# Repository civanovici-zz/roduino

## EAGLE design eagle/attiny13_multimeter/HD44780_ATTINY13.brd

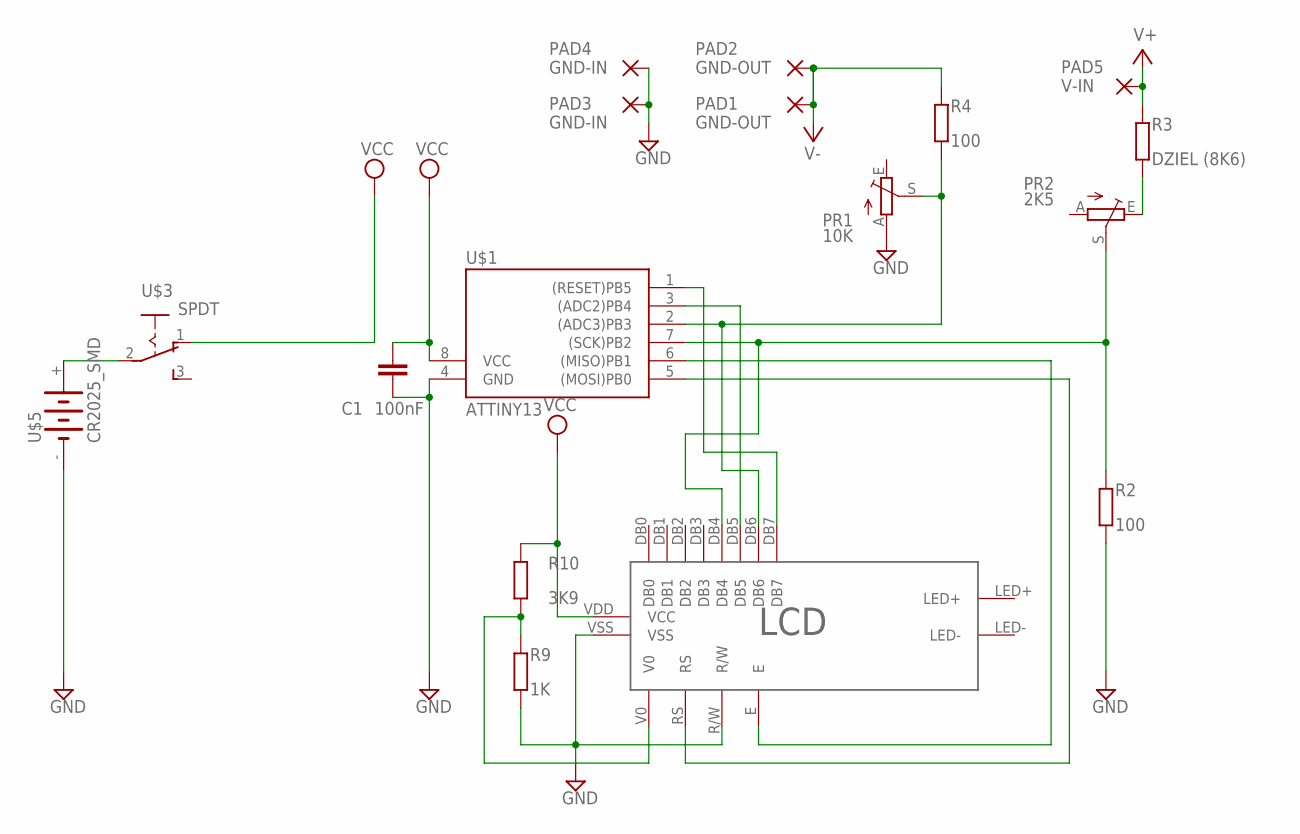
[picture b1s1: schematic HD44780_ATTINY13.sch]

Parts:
C1: 100nF; C0805
PAD1, PAD2: GND-OUT; 2,54/0,8
PAD3, PAD4: GND-IN; 2,54/0,8
PAD5: V-IN; 2,54/0,8
PR1: 10K; CA6V
PR2: 2K5; CA6V
R2, R4: 100; R0805
R3: DZIEL (8K6); R0805
R9: 1K; R0805
R10: 3K9; R0805
U$1: ATTINY13; SO08
U$2: LGDM1602N1; GDM1602N1
U$3: SPDT
U$5: CR2025_SMD

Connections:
GND: C1.2, PAD3.1, PAD4.1, PR1.A, R2.1, R9.1, U$1.4 (GND), U$2.R/W, U$2.VSS, U$5.-
unnamed: R9.2, R10.1, U$2.V0
unnamed: U$1.3 ((ADC2)PB4), U$2.DB5
unnamed: PR2.E, R3.1
unnamed: U$3.2, U$5.+
unnamed: U$1.1 ((RESET)PB5), U$2.DB7
unnamed: U$1.6 ((MISO)PB1), U$2.E
unnamed: U$1.5 ((MOSI)PB0), U$2.RS
unnamed: PR1.S, R4.1, U$1.2 ((ADC3)PB3), U$2.DB6
unnamed: PR2.S, R2.2, U$1.7 ((SCK)PB2), U$2.DB4
V+: PAD5.1, R3.2
V-: PAD1.1, PAD2.1, R4.2
VBUS: U$3.1 (O)
VCC: C1.1, R10.2, U$1.8 (VCC), U$2.VDD (VCC)

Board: 2 copper layers, 17 parts (5 on the bottom side), 13 nets, no tracks yet.

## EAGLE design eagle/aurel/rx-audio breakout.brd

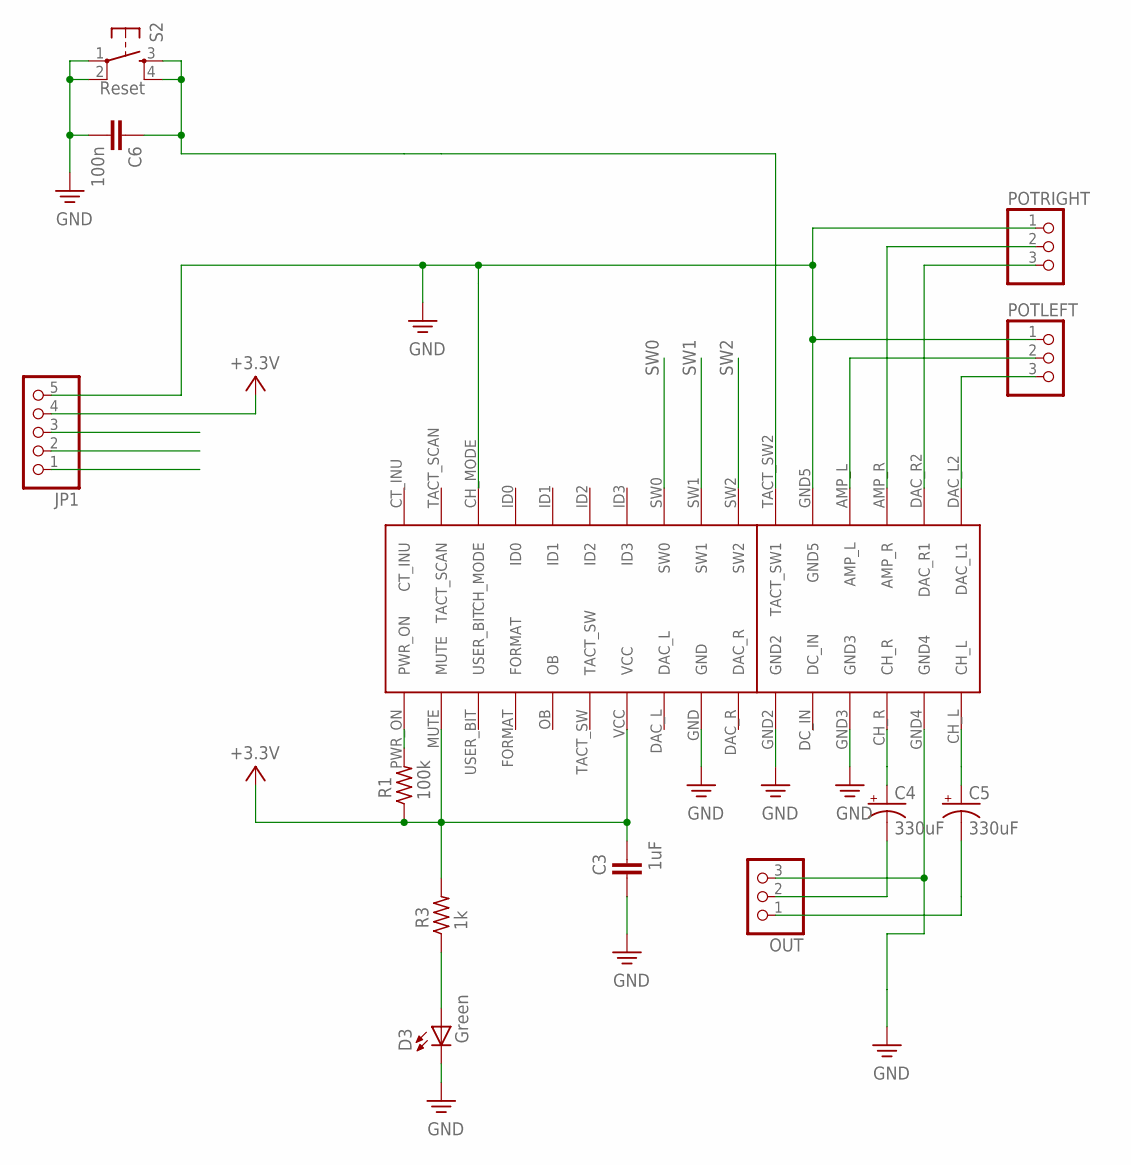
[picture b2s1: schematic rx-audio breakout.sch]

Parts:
C3: 1uF; 0805A
C4, C5: 330uF; SMC_D
C6: 100n; C0805
D3: Green; LED-0603
JP1: PINHD-1X5; 1X05
OUT: PINHD-1X3; 1X03
POTLEFT: PINHD-1X3; 1X03
POTRIGHT: PINHD-1X3; 1X03
R1: 100k; 0805A
R3: 1k; 0805A
S2: Reset; TACTILE_SWITCH_SMD
U$1: RX-AUDIO-2.4VERTICAL; AUREL_RX-AUDIO-2.4GH-TRH

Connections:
GND: C3.+ (1), C6.2, D3.C, JP1.5, OUT.3, POTLEFT.1, POTRIGHT.1, S2.1, S2.2, U$1.CH_MODE, U$1.GND, U$1.GND2, U$1.GND3, U$1.GND4, U$1.GND5
LINE_IN: C5.-, OUT.1
N2: C6.1, S2.3, S2.4, U$1.TACT_SW2 (TACT_SW1)
unnamed: C4.+, U$1.CH_R
unnamed: C5.+, U$1.CH_L
unnamed: POTLEFT.2, U$1.AMP_L
unnamed: D3.A, R3.+ (1)
unnamed: R1.- (2), U$1.PWR_ON
unnamed: POTLEFT.3, U$1.DAC_L2 (DAC_L1)
unnamed: POTRIGHT.3, U$1.DAC_R2 (DAC_R1)
unnamed: POTRIGHT.2, U$1.AMP_R
unnamed: C4.-, OUT.2
SW0: JP1.1, U$1.SW0
SW1: JP1.2, U$1.SW1
SW2: JP1.3, U$1.SW2
VCC: C3.- (2), JP1.4, R1.+ (1), R3.- (2), U$1.MUTE, U$1.VCC

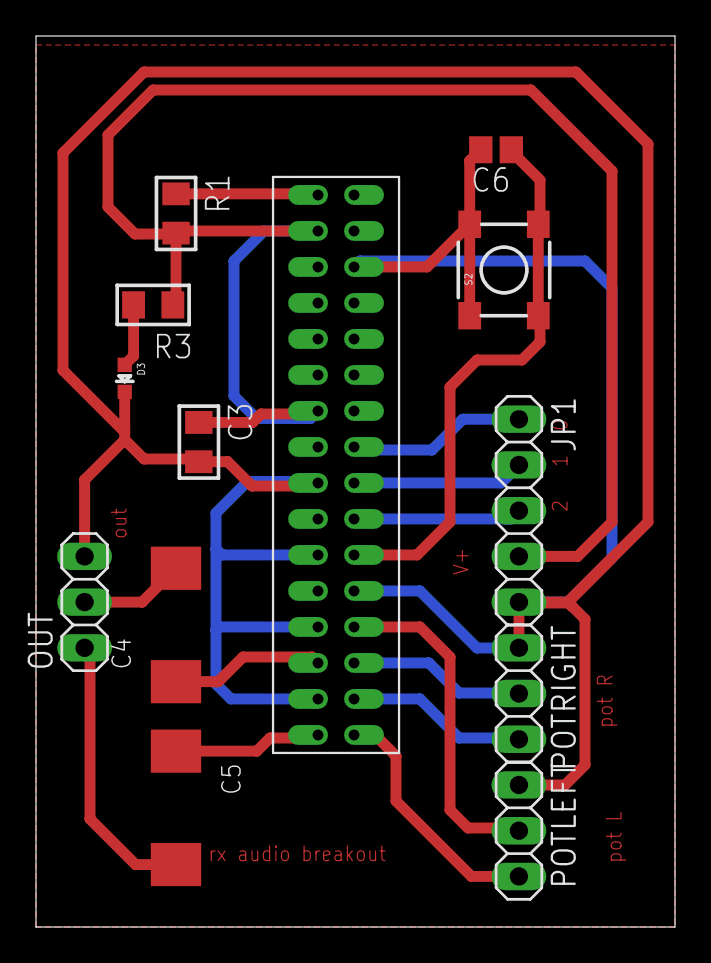
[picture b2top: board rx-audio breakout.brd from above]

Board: 2 copper layers, 35.5 x 49.5 mm, 13 parts (0 on the bottom side), 16 nets.

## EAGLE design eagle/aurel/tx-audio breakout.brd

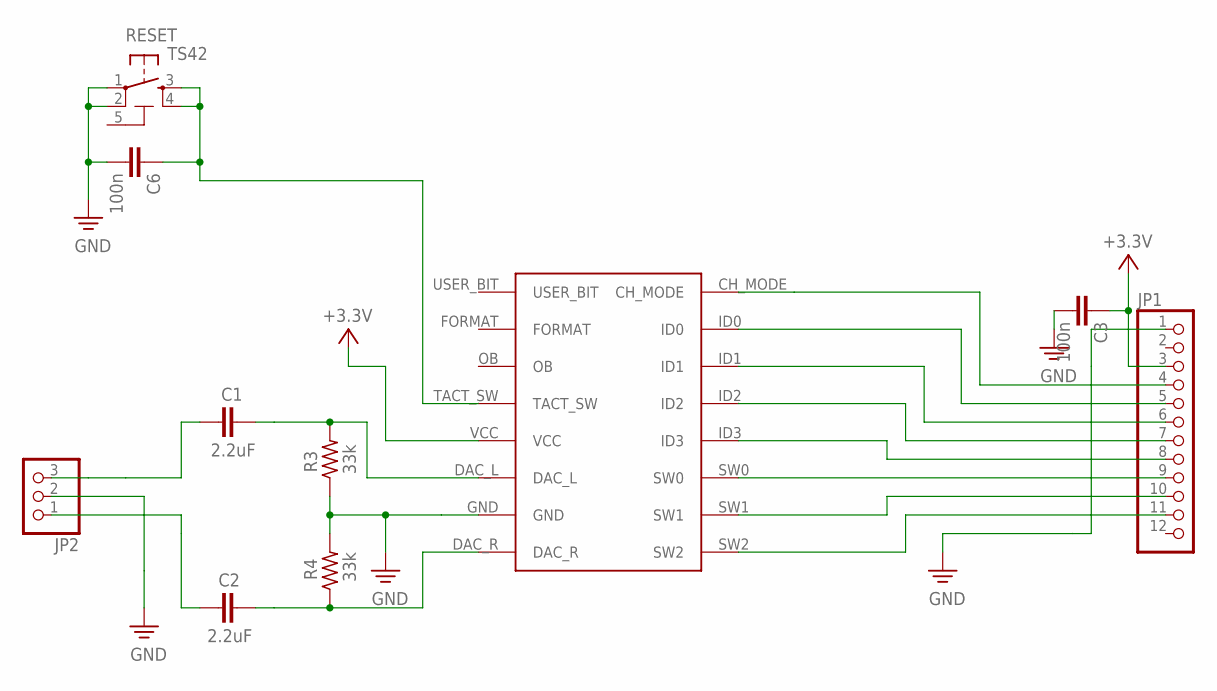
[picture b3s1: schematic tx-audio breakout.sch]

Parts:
C1, C2: 2.2uF; 0805A
C3, C6: 100n; C0805
JP1: PINHD-1X12; 1X12
JP2: PINHD-1X3; 1X03
R3, R4: 33k; 0805A
RESET: TS42
U$1: TX-AUDIO-2.4VERTICAL; AUREL-TX-AUDIO-2.4GH-TRH

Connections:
5-GND: RESET.5 (5-GND)
GND: C3.2, C6.2, JP1.1, JP2.2, R3.+ (1), R4.- (2), RESET.1, RESET.2, U$1.GND
LINE_IN: C1.+ (1), JP2.3
N2: C6.1, RESET.3, RESET.4, U$1.TACT_SW
unnamed: JP1.10, U$1.SW1
unnamed: JP1.11, U$1.SW2
unnamed: JP1.9, U$1.SW0
unnamed: C1.- (2), R3.- (2), U$1.DAC_L
unnamed: JP1.8, U$1.ID3
unnamed: JP1.7, U$1.ID2
unnamed: JP1.6, U$1.ID1
unnamed: JP1.5, U$1.ID0
unnamed: JP1.4, U$1.CH_MODE
unnamed: C2.- (2), JP2.1
unnamed: C2.+ (1), R4.+ (1), U$1.DAC_R
VCC: C3.1, JP1.3, U$1.VCC

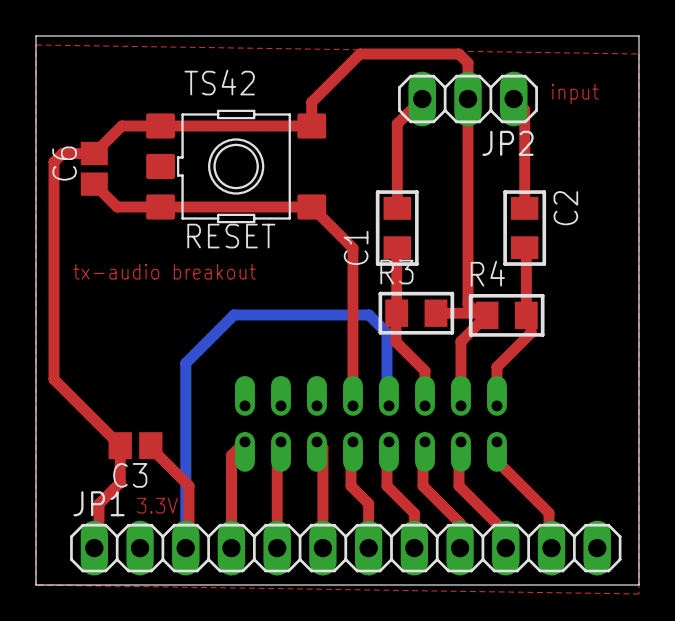
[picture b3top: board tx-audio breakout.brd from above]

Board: 2 copper layers, 33.5 x 30.5 mm, 10 parts (1 on the bottom side), 15 nets.

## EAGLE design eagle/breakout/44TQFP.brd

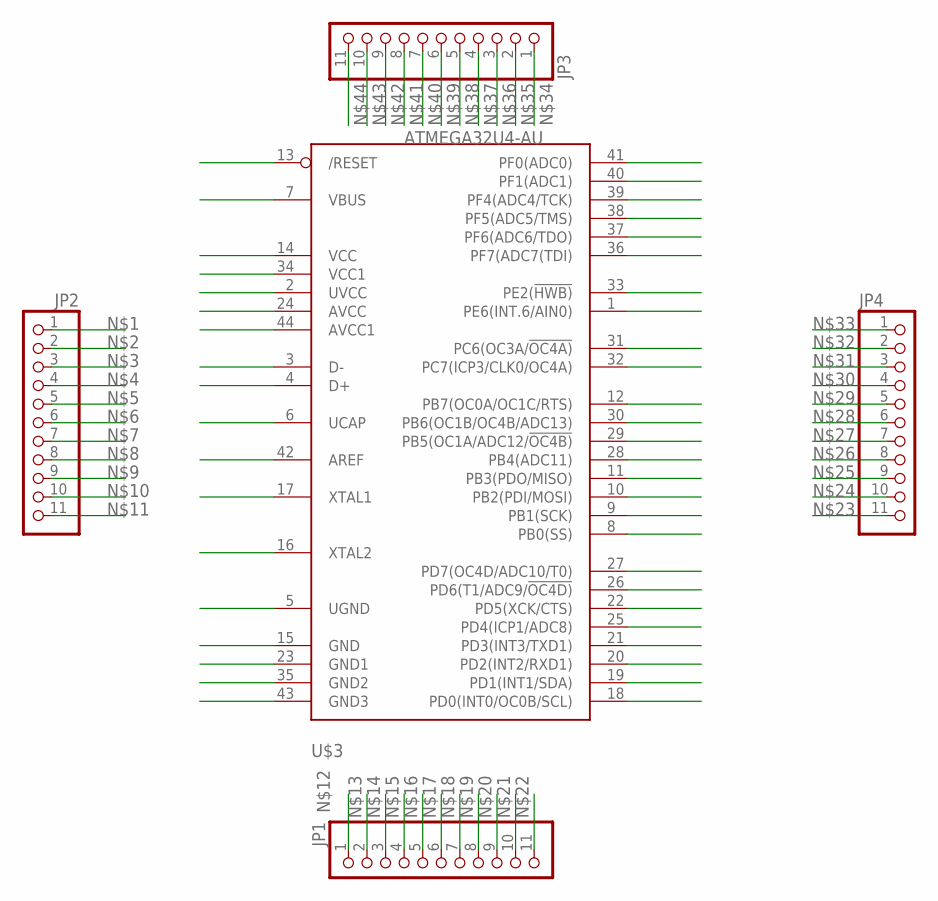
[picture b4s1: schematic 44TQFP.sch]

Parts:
JP1, JP2, JP3, JP4: PINHD-1X11; 1X11
U$3: ATMEGA32U4-AU; TQFP44

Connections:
unnamed: JP2.1, U$3.1 (PE6(INT.6/AIN0))
unnamed: JP2.2, U$3.2 (UVCC)
unnamed: JP2.3, U$3.3 (D-)
unnamed: JP2.4, U$3.4 (D+)
unnamed: JP2.5, U$3.5 (UGND)
unnamed: JP2.6, U$3.6 (UCAP)
unnamed: JP2.7, U$3.7 (VBUS)
unnamed: JP2.8, U$3.8 (PB0(SS))
unnamed: JP2.9, U$3.9 (PB1(SCK))
unnamed: JP2.10, U$3.10 (PB2(PDI/MOSI))
unnamed: JP2.11, U$3.11 (PB3(PDO/MISO))
unnamed: JP1.1, U$3.12 (PB7(OC0A/OC1C/RTS))
unnamed: JP1.2, U$3.13 (/RESET)
unnamed: JP1.3, U$3.14 (VCC)
unnamed: JP1.4, U$3.15 (GND)
unnamed: JP1.5, U$3.16 (XTAL2)
unnamed: JP1.6, U$3.17 (XTAL1)
unnamed: JP1.7, U$3.18 (PD0(INT0/OC0B/SCL))
unnamed: JP1.8, U$3.19 (PD1(INT1/SDA))
unnamed: JP1.9, U$3.20 (PD2(INT2/RXD1))
unnamed: JP1.10, U$3.21 (PD3(INT3/TXD1))
unnamed: JP1.11, U$3.22 (PD5(XCK/CTS))
unnamed: JP4.11, U$3.23 (GND1)
unnamed: JP4.10, U$3.24 (AVCC)
unnamed: JP4.9, U$3.25 (PD4(ICP1/ADC8))
unnamed: JP4.8, U$3.26 (PD6(T1/ADC9/!OC4D))
unnamed: JP4.7, U$3.27 (PD7(OC4D/ADC10/T0))
unnamed: JP4.6, U$3.28 (PB4(ADC11))
unnamed: JP4.5, U$3.29 (PB5(OC1A/ADC12/!OC4B))
unnamed: JP4.4, U$3.30 (PB6(OC1B/OC4B/ADC13))
unnamed: JP4.3, U$3.31 (PC6(OC3A/!OC4A))
unnamed: JP4.2, U$3.32 (PC7(ICP3/CLK0/OC4A))
unnamed: JP4.1, U$3.33 (PE2(!HWB))
unnamed: JP3.1, U$3.34 (VCC1)
unnamed: JP3.2, U$3.35 (GND2)
unnamed: JP3.3, U$3.36 (PF7(ADC7(TDI))
unnamed: JP3.4, U$3.37 (PF6(ADC6/TDO))
unnamed: JP3.5, U$3.38 (PF5(ADC5/TMS))
unnamed: JP3.6, U$3.39 (PF4(ADC4/TCK))
unnamed: JP3.7, U$3.40 (PF1(ADC1))
unnamed: JP3.8, U$3.41 (PF0(ADC0))
unnamed: JP3.9, U$3.42 (AREF)
unnamed: JP3.10, U$3.43 (GND3)
unnamed: JP3.11, U$3.44 (AVCC1)

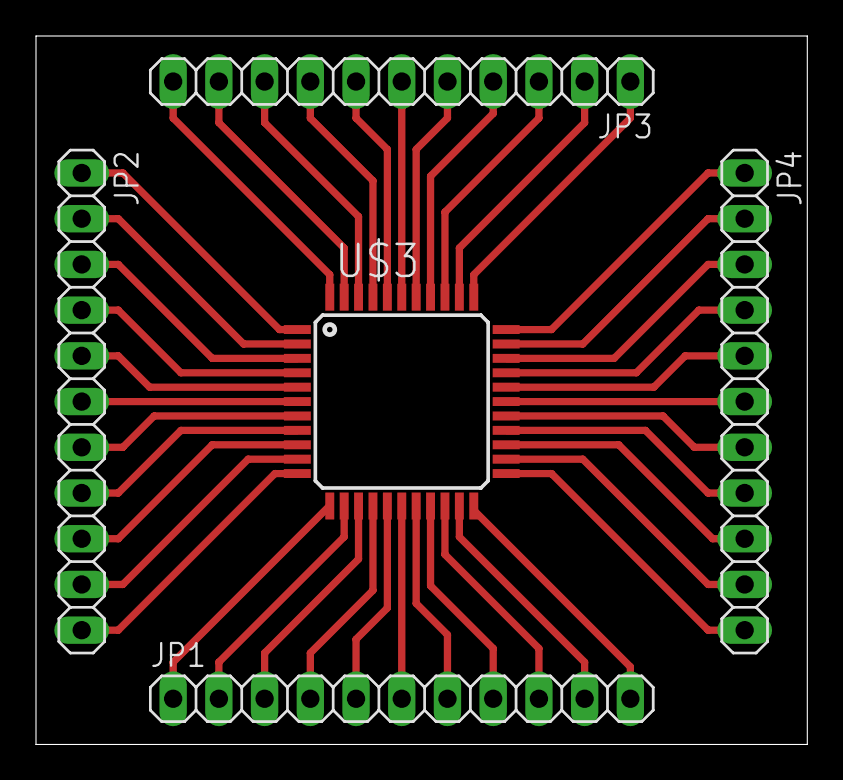
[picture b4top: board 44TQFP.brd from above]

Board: 2 copper layers, 42.9 x 39.4 mm, 5 parts (0 on the bottom side), 44 nets.

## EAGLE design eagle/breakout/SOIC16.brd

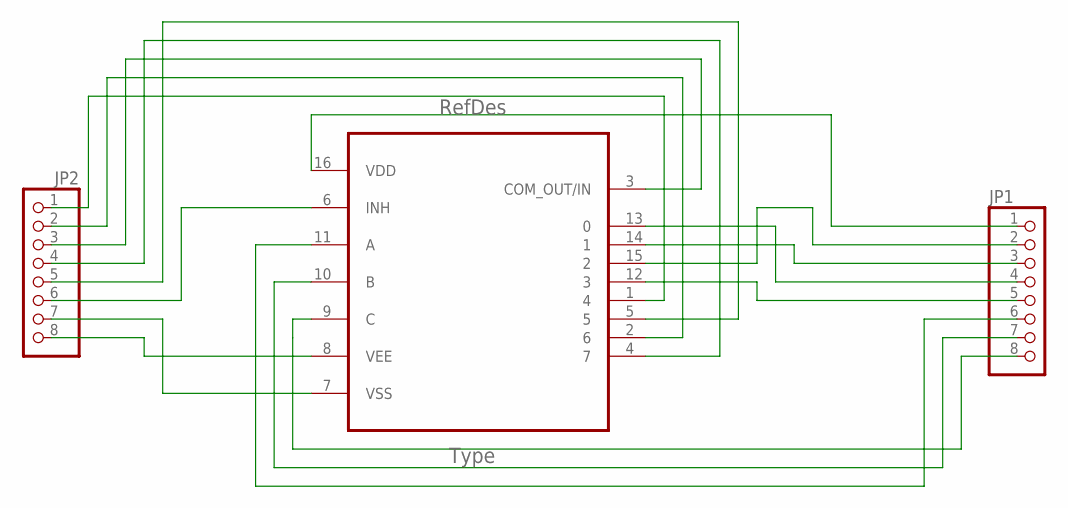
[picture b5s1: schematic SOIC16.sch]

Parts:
JP1, JP2: PINHD-1X8; 1X08
U1: CD4051BM; SOIC127P600X175-16N

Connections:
unnamed: JP2.1, U1.1 (4)
unnamed: JP2.2, U1.2 (6)
unnamed: JP2.3, U1.3 (COM_OUT/IN)
unnamed: JP2.4, U1.4 (7)
unnamed: JP2.5, U1.5
unnamed: JP2.6, U1.6 (INH)
unnamed: JP2.7, U1.7 (VSS)
unnamed: JP2.8, U1.8 (VEE)
unnamed: JP1.8, U1.9 (C)
unnamed: JP1.7, U1.10 (B)
unnamed: JP1.6, U1.11 (A)
unnamed: JP1.5, U1.12 (3)
unnamed: JP1.4, U1.13 (0)
unnamed: JP1.3, U1.14 (1)
unnamed: JP1.2, U1.15 (2)
unnamed: JP1.1, U1.16 (VDD)

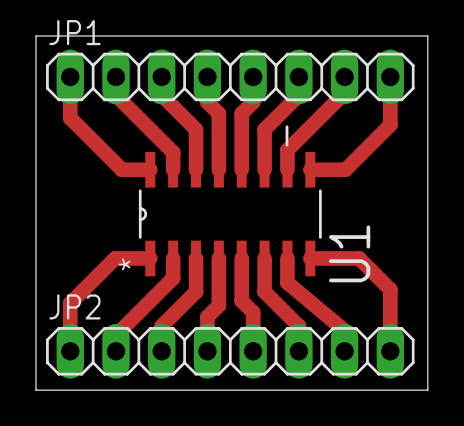
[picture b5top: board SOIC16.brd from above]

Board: 2 copper layers, 21.8 x 19.7 mm, 3 parts (0 on the bottom side), 16 nets.
